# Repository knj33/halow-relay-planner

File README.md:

# HaLow Relay Planner (Earth / Moon / Mars)

A browser prototype for planning Wi-Fi HaLow relay deployments between two surface points, A and B, on Earth, the Moon or Mars. It runs on one seamless, Google-Earth-style globe: click the surface to place nodes, stream real elevation for the resulting planning area, place relays, check every link against terrain and a link budget, attach base stations to the nearest visible satellite, and compare the relay plan with conventional alternatives.

It is a communications planning prototype. It has not been checked against the full requirements of any particular NASA Space Apps challenge.

## Run it

Requires Node 20 or newer.

```bash
npm install
npm run dev        # http://localhost:5173
npm test           # engine and store tests (Vitest)
make -C native test # native request, failure and thread-pool regression tests
npm run build      # type-check + production build in dist/
npm run preview    # serve the production build
```

## Presenting

The site can play slide decks, PowerPoint style, including **live slides** where the planner itself is on screen and the deck drives it. Open `http://localhost:5173/#/present`, click **Present** in the masthead, or press `P`; `?` lists the controls. Only a sample deck exists so far. How to write a deck and how the engine works: [docs/PRESENTATION.md](docs/PRESENTATION.md). How the app stays smooth on slow CPUs: [docs/PERFORMANCE.md](docs/PERFORMANCE.md).

No backend, accounts or API keys. Imagery, elevation and the lunar and Martian DEMs stream public data over the internet; the bundled base maps and synthetic terrain work offline.

## Data sources by body

| Body | Planning elevation (fallbacks in order) | Globe imagery |
|---|---|---|
| Earth | Mapzen Terrain Tiles on AWS | Sentinel-2 cloudless (EOX) |
| Moon | USGS LRO LOLA 118 m → bundled LOLA 16 px/deg | LRO WAC mosaic via NASA Moon Trek |
| Mars | USGS HRSC + MOLA blend 200 m → USGS MOLA 463 m → bundled MOLA MEGDR 16 px/deg | Viking MDIM 2.1 colour mosaic via NASA Mars Trek |

The bundled Mars assets are rebuilt with `node scripts/build-mars-tiles.mjs <megt90n000eb.img>` (NASA PDS MOLA MEGDR) and `python scripts/build-trek-base.py <Mars Trek tile URL> public/base/mars.jpg 2`.

## Optional native Relay Engine

The planner works on its own. It can also use a small native helper, built from `native/` in C for x86-64-v3 (`-O3 -march=x86-64-v3 -mtune=native -flto`), which downloads and resamples terrain with a thread pool and returns a compact binary grid over loopback.

```bash
sudo apt install build-essential libcurl4-openssl-dev libpng-dev   # Debian / Ubuntu
cd native
make
make install           # optional: ~/.local/bin/relay-engine, no sudo
./relay-engine          # http://127.0.0.1:8765
```

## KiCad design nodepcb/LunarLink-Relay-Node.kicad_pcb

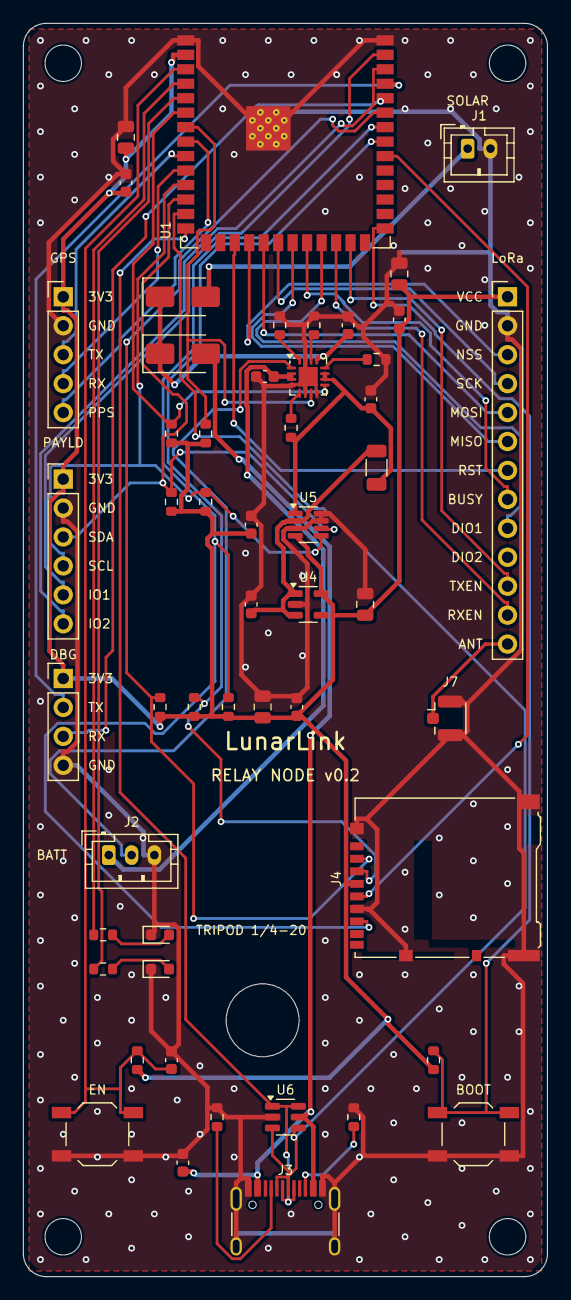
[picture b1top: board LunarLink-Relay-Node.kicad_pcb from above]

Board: 2 copper layers, 46.0 x 110.0 mm, 57 parts (0 on the bottom side), 48 nets.

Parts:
C1, C5, C9: 1u; C_0603_1608Metric
C2, C3, C14: 4.7u; C_0603_1608Metric
C4, C8, C11, C13: 100n; C_0603_1608Metric
C6, C7, C10, C12: 10u; C_0805_2012Metric
D1, D2: SS34; D_SMA
D3: GREEN status; LED_0603_1608Metric
D4: BLUE mesh link; LED_0603_1608Metric
H1, H2, H3, H4: MountingHole_3.2mm_M3
H5: Tripod 1/4-20; MountingHole_6.4mm_M6
J1: Solar panel 5-6V; JST_PH_B2B-PH-K_1x02_P2.00mm_Vertical
J2: 1S Li-ion + 10k NTC; JST_PH_B3B-PH-K_1x03_P2.00mm_Vertical
J3: USB-C 2.0; USB_C_HRO_TYPE-C-31-M-12_BoardEdge
J4: microSD socket; microSD_HC_Hirose_DM3AT-SF-PEJM5
J5: GPS module (u-blox M8/M10); PinHeader_1x05_P2.54mm_Vertical
J6: Science payload port; PinHeader_1x06_P2.54mm_Vertical
J7: u.FL → 868/915 MHz antenna; U.FL_Hirose_U.FL-R-SMT-1_Vertical
J8: UART debug; PinHeader_1x04_P2.54mm_Vertical
R1: 1.18k (ILIM≈1.3A); R_0603_1608Metric
R2: 1.5k (ICHG≈600mA); R_0603_1608Metric
R3: 46.4k (timer); R_0603_1608Metric
R4: 0.1R 1% (shunt); R_1206_3216Metric
R5, R6, R7, R8, R9, R10, R11: 10k; R_0603_1608Metric
R12, R13: 5.1k; R_0603_1608Metric
R14, R15: 4.7k; R_0603_1608Metric
R16, R17: 1k; R_0603_1608Metric
R18: 10k (EN2 pull-up); R_0603_1608Metric
SW1: RESET; SW_SPST_TL3342
SW2: BOOT; SW_SPST_TL3342
U1: ESP32-S3-WROOM-1-N8; ESP32-S3-WROOM-1_BoardEdge
U2: SX1262 module (e.g. Ebyte E22-900M22S); PinHeader_1x13_P2.54mm_Vertical
U3: BQ24074RGT; VQFN-16-1EP_3x3mm_P0.5mm_EP1.68x1.68mm
U4: AP2112K-3.3; SOT-23-5
U5: INA219AIDCNR; SOT-23-8
U6: USBLC6-2SC6 (ESD); SOT-23-6

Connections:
+3V3: C4.1, C6.1, C7.1, C8.1, C10.1, C11.1, C12.1, C13.1, J4.4, J5.1, J6.1, J8.1, R5.1, R6.1, R7.1, R8.1, R9.1, R10.1, R11.1, R14.1, R15.1, U1.2, U2.1, U4.5, U5.4
BAT_NTC: J2.2, U3.1
BQ_EN2: R18.2, U3.5
BQ_ILIM: R1.1, U3.12
BQ_ISET: R2.1, U3.16
BQ_TMR: R3.1, U3.14
CHG_N: R5.2, U1.6, U3.9
ESP_BOOT: R8.2, SW2.1, U1.27
ESP_EN: C9.1, R7.2, SW1.1, U1.3
GND: C1.2, C2.2, C3.2, C4.2, C5.2, C6.2, C7.2, C8.2, C9.2, C10.2, C11.2, C12.2, C13.2, C14.2, D3.1, D4.1, J1.2, J2.3, J3.A1, J3.A12, J3.B1, J3.B12, J3.S1, J4.6, J4.11, J5.2, J6.2, J7.2, J8.4, R1.2, R2.2, R3.2, R12.2, R13.2, SW1.2, SW2.2, U1.1, U1.40, U1.41, U2.2, U3.4, U3.6, U3.8, U3.15, U3.17, U4.2, U5.3, U5.7, U5.8, U6.2
GPS_PPS: J5.5, U1.8
GPS_RXD: J5.4, U1.10
GPS_TXD: J5.3, U1.9
I2C_SCL: J6.4, R15.2, U1.11, U5.5
I2C_SDA: J6.3, R14.2, U1.12, U5.6
LED1_A: D3.2, R16.2
LED2_A: D4.2, R17.2
LED_LINK: R17.1, U1.5
LED_STATUS: R16.1, U1.4
LORA_BUSY: U1.22, U2.8
LORA_DIO1: U1.23, U2.9
LORA_MISO: U1.21, U2.6
LORA_MOSI: U1.19, U2.5
LORA_NRST: U1.17, U2.7
LORA_NSS: U1.18, U2.3
LORA_RXEN: U1.24, U2.12
LORA_SCK: U1.20, U2.4
LORA_TXEN: U1.25, U2.11
PAYLOAD_IO1: J6.5, U1.39
PAYLOAD_IO2: J6.6, U1.38
PGOOD_N: R6.2, U1.7, U3.7
RF_ANT: J7.1, U2.13
SD_CS: J4.2, R9.2, U1.35
SD_MISO: J4.7, R11.2, U1.34
SD_MOSI: J4.3, R10.2, U1.33
SD_SCK: J4.5, U1.32
SOLAR_IN: D1.2, J1.1
UART0_RX: J8.3, U1.36
UART0_TX: J8.2, U1.37
USB_CC1: J3.A5, R12.1
USB_CC2: J3.B5, R13.1
USB_DN: J3.A7, J3.B7, U1.13, U6.3, U6.4
USB_DP: J3.A6, J3.B6, U1.14, U6.1, U6.6
VBAT: C3.1, J2.1, U3.2, U3.3
VBUS: C14.1, D2.2, J3.A4, J3.A9, J3.B4, J3.B9, U6.5
VIN_CHG: C1.1, D1.1, D2.1, U3.13
VSYS: C2.1, R4.1, R18.1, U3.10, U3.11, U5.1
VSYS_MON: C5.1, R4.2, U4.1, U4.3, U5.2
